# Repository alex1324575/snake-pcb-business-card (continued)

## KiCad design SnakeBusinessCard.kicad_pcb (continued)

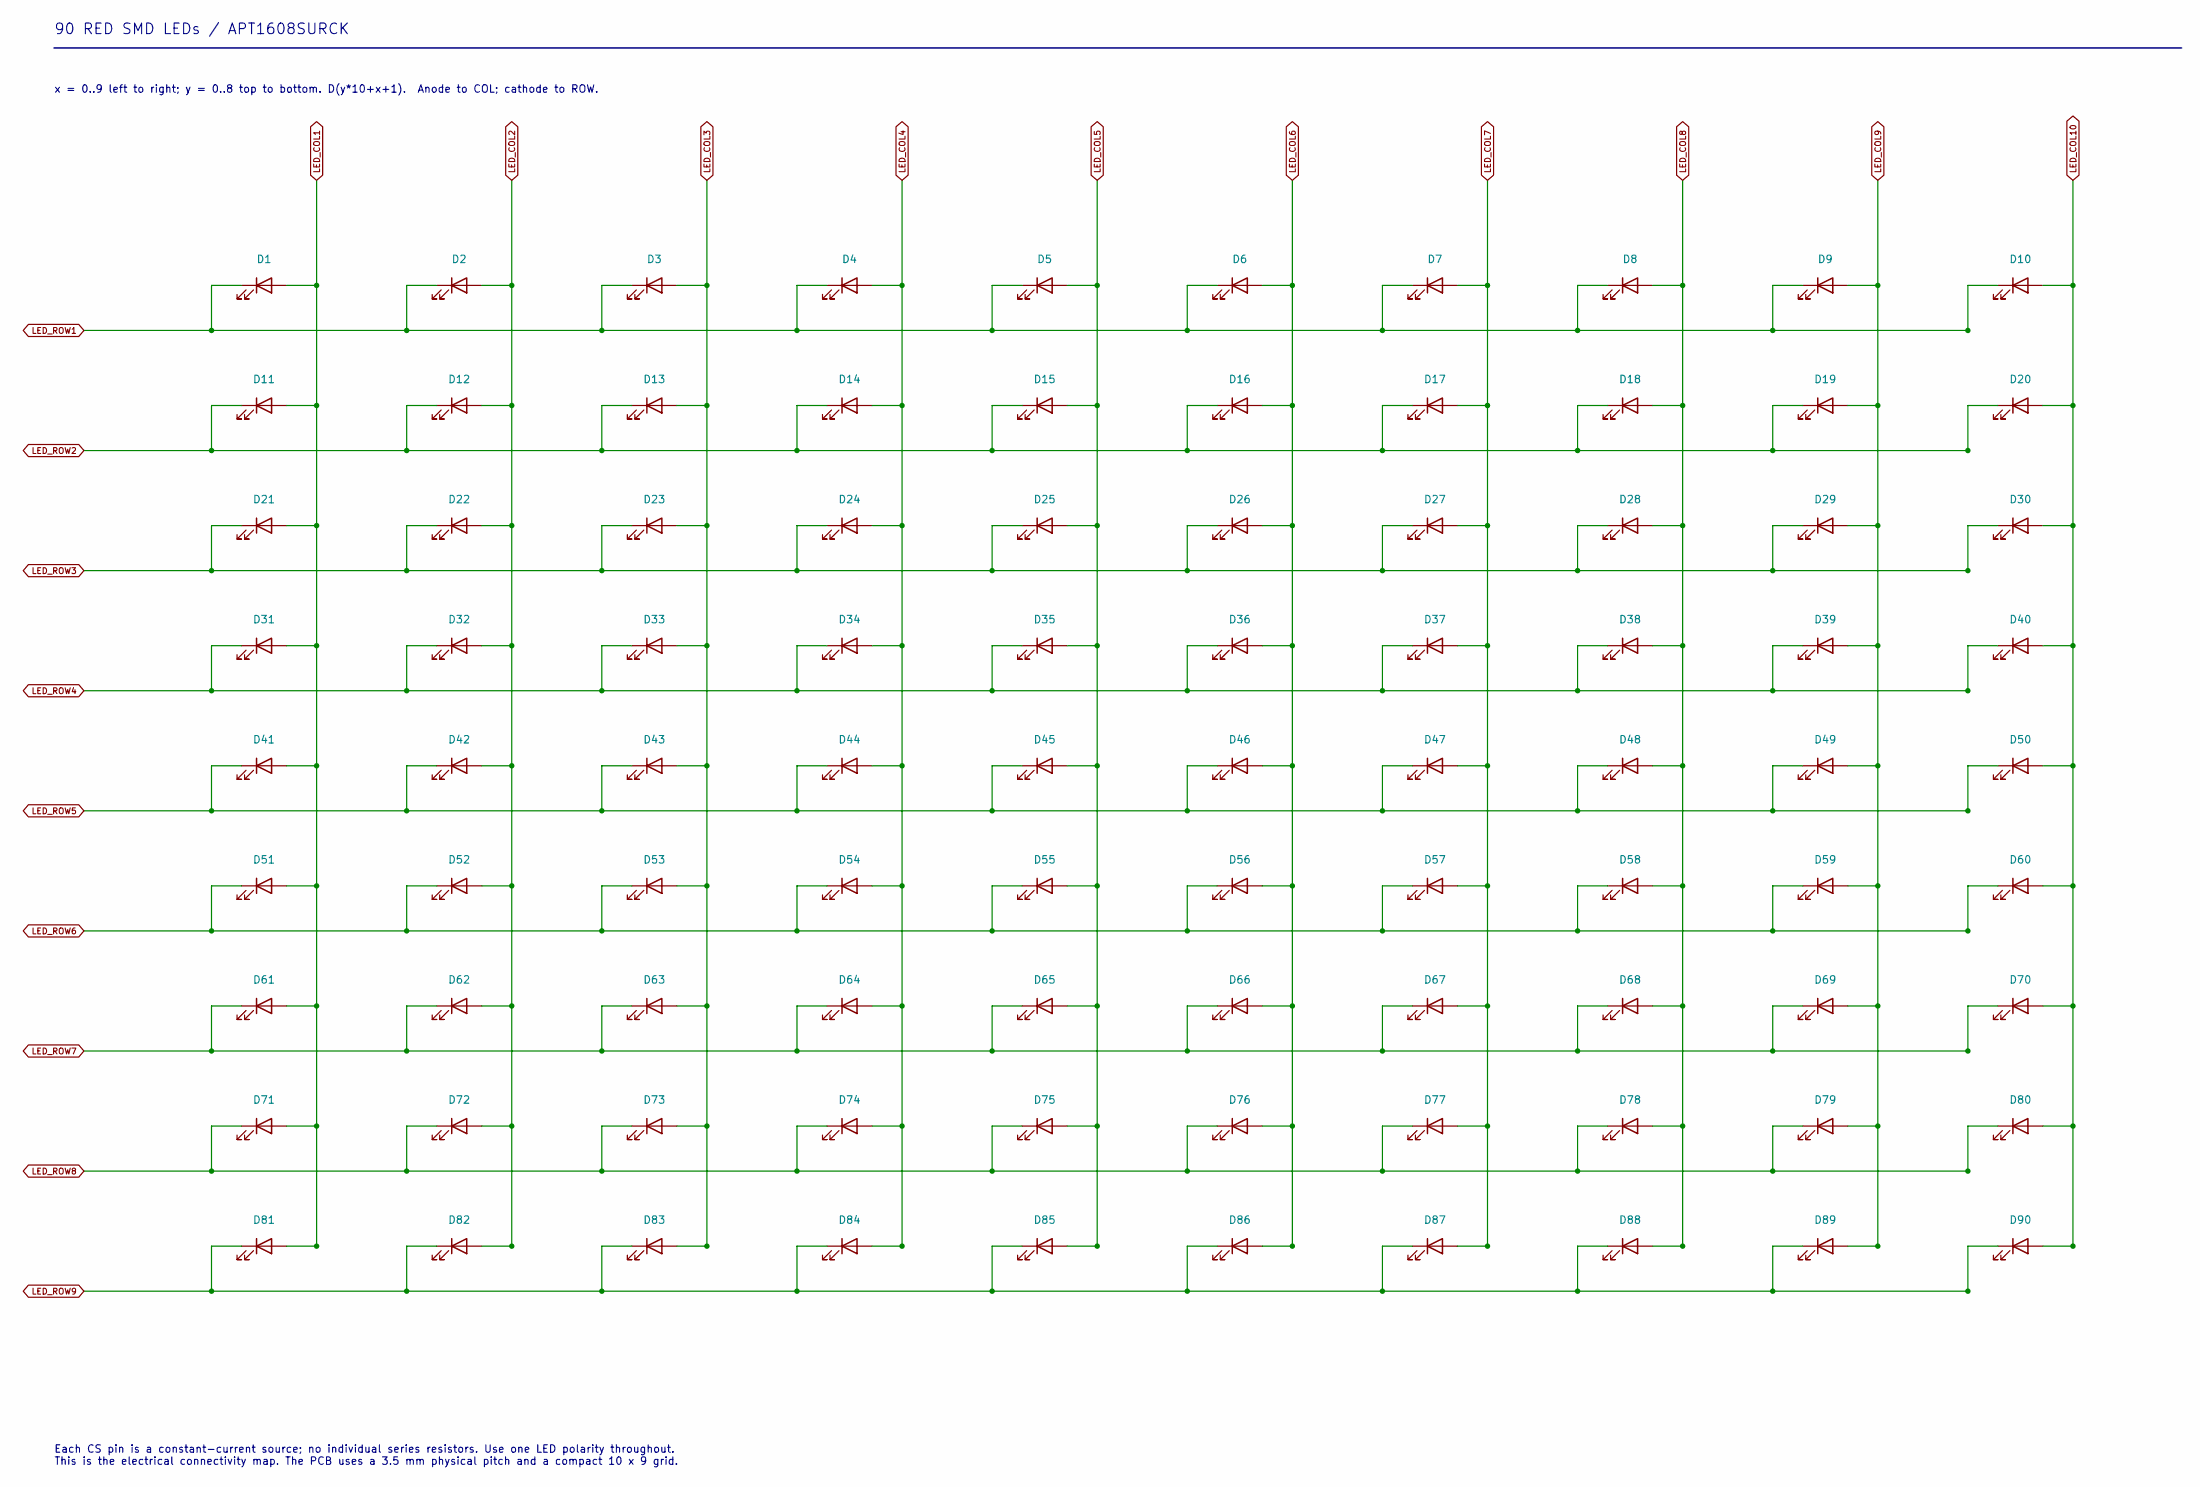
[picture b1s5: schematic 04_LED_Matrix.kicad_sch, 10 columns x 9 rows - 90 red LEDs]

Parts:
D1, D2, D3, D4, D5, D6, D7, D8, D9, D10, D11, D12, D13, D14, D15, D16, D17, D18, D19, D20, D21, D22, D23, D24, D25, D26, D27, D28, D29, D30, D31, D32, D33, D34, D35, D36, D37, D38, D39, D40, D41, D42, D43, D44, D45, D46, D47, D48, D49, D50, D51, D52, D53, D54, D55, D56, D57, D58, D59, D60, D61, D62, D63, D64, D65, D66, D67, D68, D69, D70, D71, D72, D73, D74, D75, D76, D77, D78, D79, D80, D81, D82, D83, D84, D85, D86, D87, D88, D89, D90: RED; Kingbright_APT1608SURCK; MPN APT1608SURCK

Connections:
LED_COL1: D1.2 (A), D11.2 (A), D21.2 (A), D31.2 (A), D41.2 (A), D51.2 (A), D61.2 (A), D71.2 (A), D81.2 (A); also elsewhere on the board
LED_COL2: D2.2 (A), D12.2 (A), D22.2 (A), D32.2 (A), D42.2 (A), D52.2 (A), D62.2 (A), D72.2 (A), D82.2 (A); also elsewhere on the board
LED_COL3: D3.2 (A), D13.2 (A), D23.2 (A), D33.2 (A), D43.2 (A), D53.2 (A), D63.2 (A), D73.2 (A), D83.2 (A); also elsewhere on the board
LED_COL4: D4.2 (A), D14.2 (A), D24.2 (A), D34.2 (A), D44.2 (A), D54.2 (A), D64.2 (A), D74.2 (A), D84.2 (A); also elsewhere on the board
LED_COL5: D5.2 (A), D15.2 (A), D25.2 (A), D35.2 (A), D45.2 (A), D55.2 (A), D65.2 (A), D75.2 (A), D85.2 (A); also elsewhere on the board
LED_COL6: D6.2 (A), D16.2 (A), D26.2 (A), D36.2 (A), D46.2 (A), D56.2 (A), D66.2 (A), D76.2 (A), D86.2 (A); also elsewhere on the board
LED_COL7: D7.2 (A), D17.2 (A), D27.2 (A), D37.2 (A), D47.2 (A), D57.2 (A), D67.2 (A), D77.2 (A), D87.2 (A); also elsewhere on the board
LED_COL8: D8.2 (A), D18.2 (A), D28.2 (A), D38.2 (A), D48.2 (A), D58.2 (A), D68.2 (A), D78.2 (A), D88.2 (A); also elsewhere on the board
LED_COL9: D9.2 (A), D19.2 (A), D29.2 (A), D39.2 (A), D49.2 (A), D59.2 (A), D69.2 (A), D79.2 (A), D89.2 (A); also elsewhere on the board
LED_COL10: D10.2 (A), D20.2 (A), D30.2 (A), D40.2 (A), D50.2 (A), D60.2 (A), D70.2 (A), D80.2 (A), D90.2 (A); also elsewhere on the board
LED_ROW1: D1.1 (K), D2.1 (K), D3.1 (K), D4.1 (K), D5.1 (K), D6.1 (K), D7.1 (K), D8.1 (K), D9.1 (K), D10.1 (K); also elsewhere on the board
LED_ROW2: D11.1 (K), D12.1 (K), D13.1 (K), D14.1 (K), D15.1 (K), D16.1 (K), D17.1 (K), D18.1 (K), D19.1 (K), D20.1 (K); also elsewhere on the board
LED_ROW3: D21.1 (K), D22.1 (K), D23.1 (K), D24.1 (K), D25.1 (K), D26.1 (K), D27.1 (K), D28.1 (K), D29.1 (K), D30.1 (K); also elsewhere on the board
LED_ROW4: D31.1 (K), D32.1 (K), D33.1 (K), D34.1 (K), D35.1 (K), D36.1 (K), D37.1 (K), D38.1 (K), D39.1 (K), D40.1 (K); also elsewhere on the board
LED_ROW5: D41.1 (K), D42.1 (K), D43.1 (K), D44.1 (K), D45.1 (K), D46.1 (K), D47.1 (K), D48.1 (K), D49.1 (K), D50.1 (K); also elsewhere on the board
LED_ROW6: D51.1 (K), D52.1 (K), D53.1 (K), D54.1 (K), D55.1 (K), D56.1 (K), D57.1 (K), D58.1 (K), D59.1 (K), D60.1 (K); also elsewhere on the board
LED_ROW7: D61.1 (K), D62.1 (K), D63.1 (K), D64.1 (K), D65.1 (K), D66.1 (K), D67.1 (K), D68.1 (K), D69.1 (K), D70.1 (K); also elsewhere on the board
LED_ROW8: D71.1 (K), D72.1 (K), D73.1 (K), D74.1 (K), D75.1 (K), D76.1 (K), D77.1 (K), D78.1 (K), D79.1 (K), D80.1 (K); also elsewhere on the board
LED_ROW9: D81.1 (K), D82.1 (K), D83.1 (K), D84.1 (K), D85.1 (K), D86.1 (K), D87.1 (K), D88.1 (K), D89.1 (K), D90.1 (K); also elsewhere on the board

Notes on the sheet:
90 RED SMD LEDs / APT1608SURCK
x = 0..9 left to right; y = 0..8 top to bottom. D(y*10+x+1). Anode to COL; cathode to ROW.
Each CS pin is a constant-current source; no individual series resistors. Use one LED polarity throughout. This is the electrical connectivity map. The PCB uses a 3.5 mm physical pitch and a compact 10 x 9 grid.

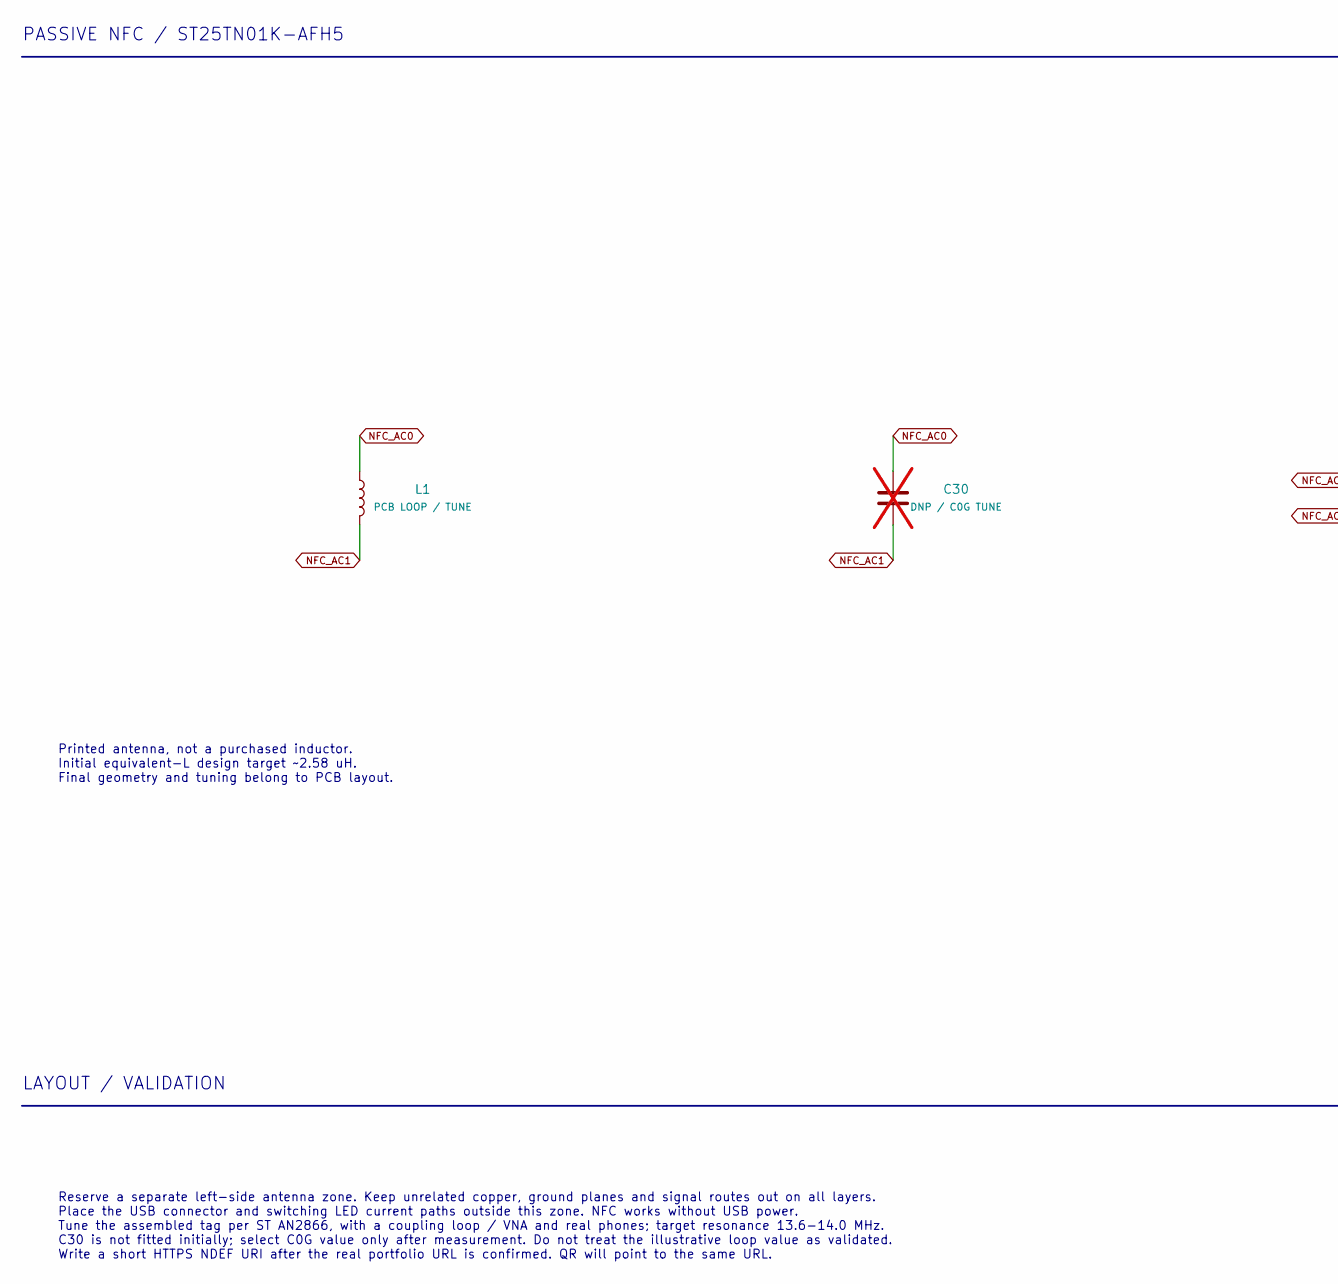
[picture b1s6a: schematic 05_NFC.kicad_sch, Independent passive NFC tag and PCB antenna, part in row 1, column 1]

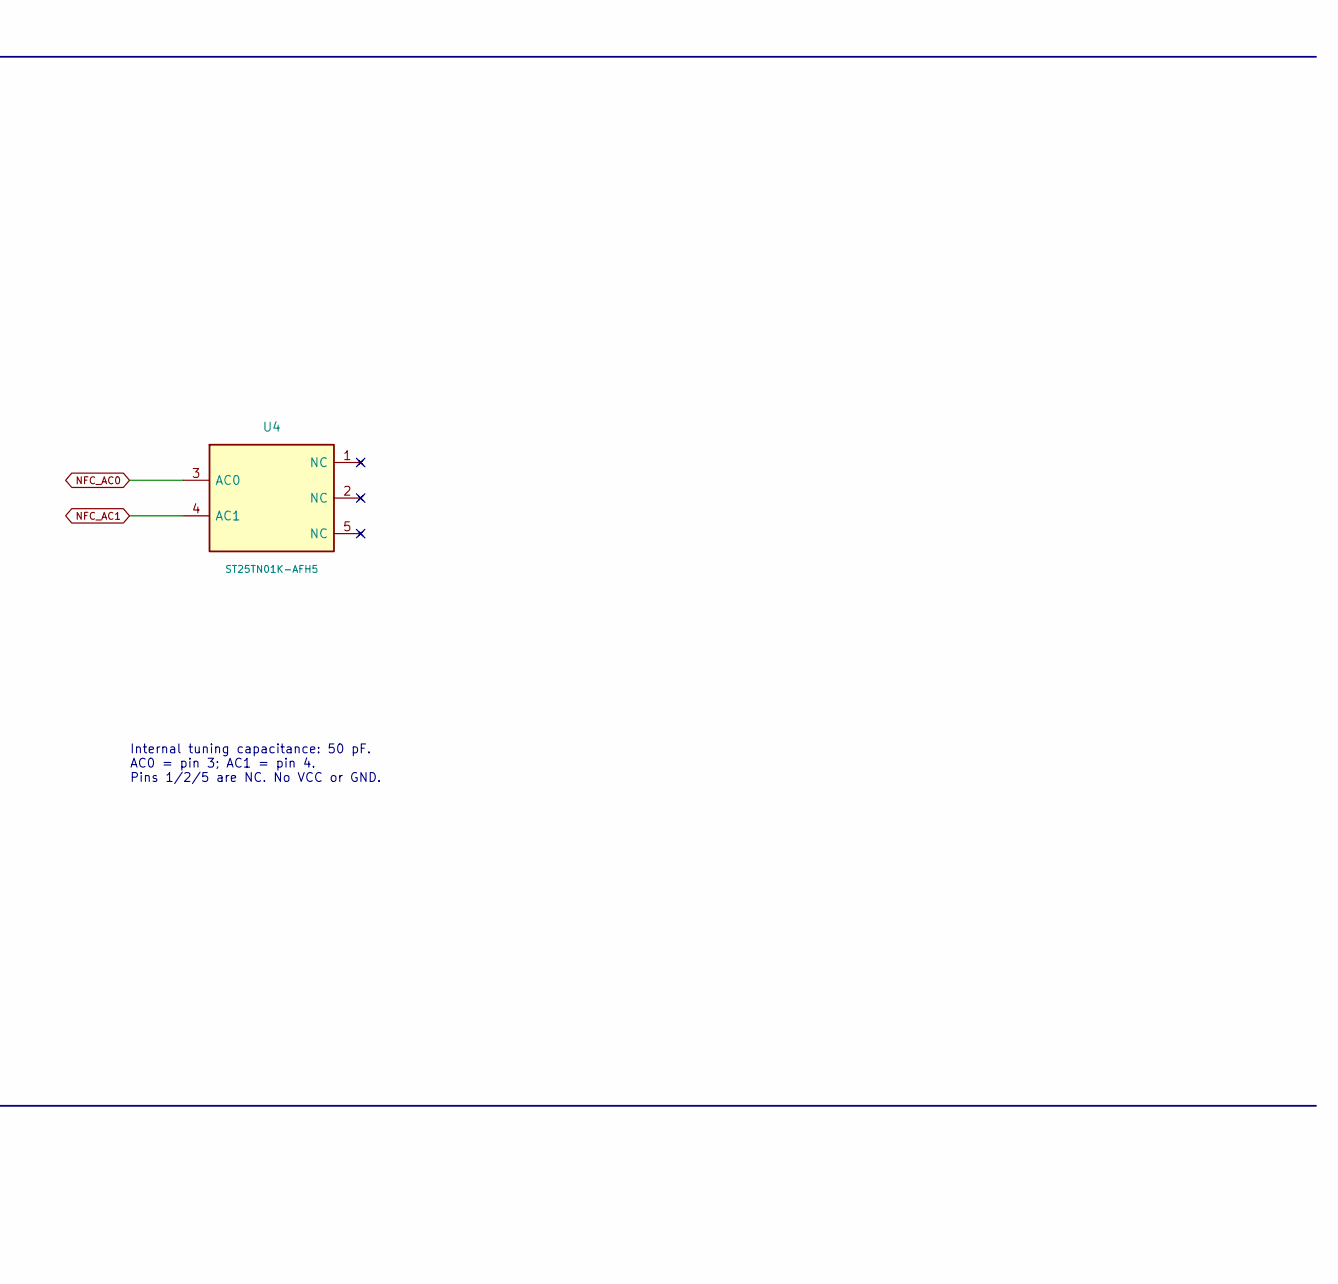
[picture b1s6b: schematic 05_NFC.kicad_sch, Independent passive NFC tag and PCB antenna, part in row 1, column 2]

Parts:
C30: DNP / C0G TUNE; C_0603_1608Metric; not fitted
L1: PCB LOOP / TUNE
U4: ST25TN01K-AFH5; ST25TN01K_UFDFPN5_1.7x1.4mm; MPN ST25TN01K-AFH5

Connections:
NFC_AC0: C30.1, L1.1, U4.3 (AC0); also elsewhere on the board
NFC_AC1: C30.2, L1.2, U4.4 (AC1); also elsewhere on the board

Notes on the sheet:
PASSIVE NFC / ST25TN01K-AFH5
Printed antenna, not a purchased inductor. Initial equivalent-L design target ~2.58 uH. Final geometry and tuning belong to PCB layout.
Internal tuning capacitance: 50 pF. AC0 = pin 3; AC1 = pin 4. Pins 1/2/5 are NC. No VCC or GND.
LAYOUT / VALIDATION
Reserve a separate left-side antenna zone. Keep unrelated copper, ground planes and signal routes out on all layers. Place the USB connector and switching LED current paths outside this zone. NFC works without USB power. Tune the assembled tag per ST AN2866, with a coupling loop / VNA and real phon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

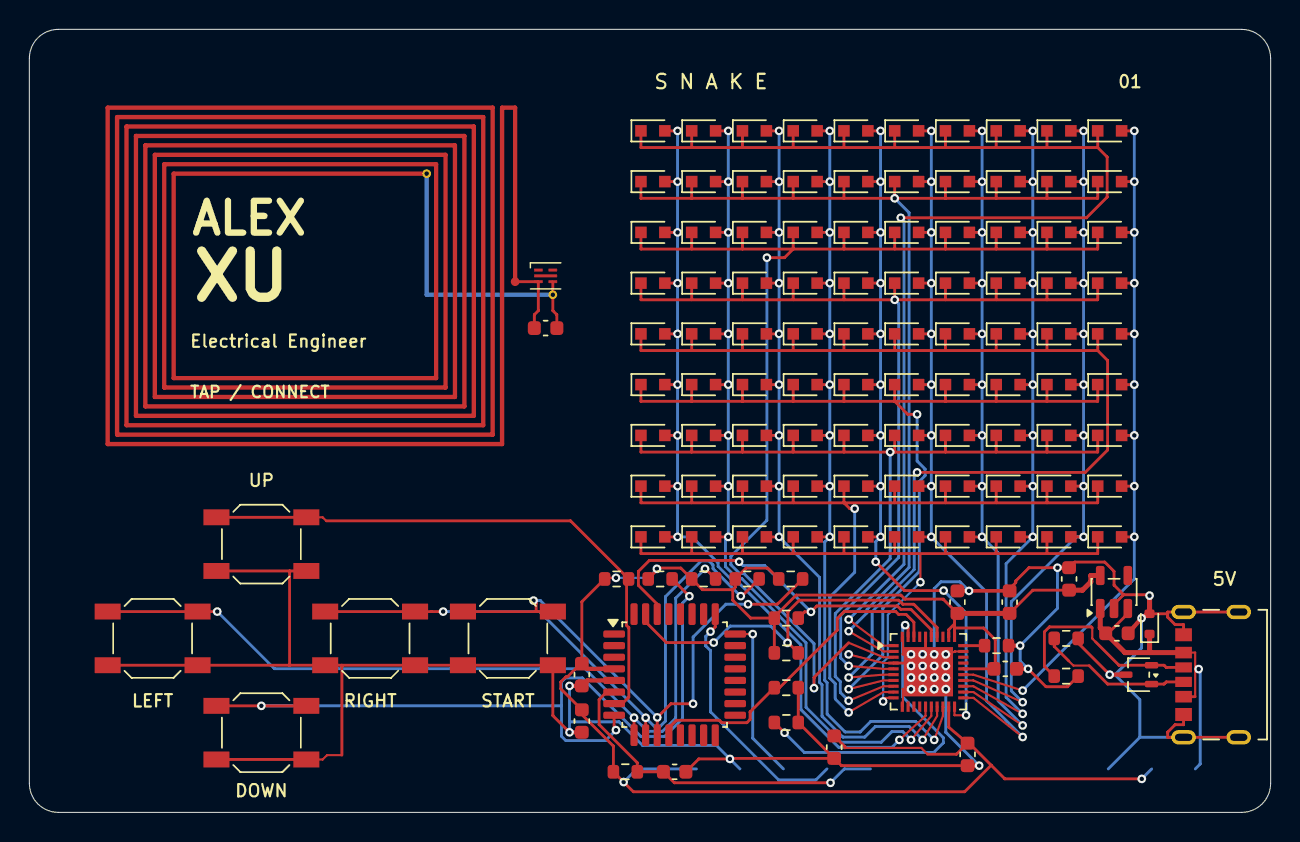
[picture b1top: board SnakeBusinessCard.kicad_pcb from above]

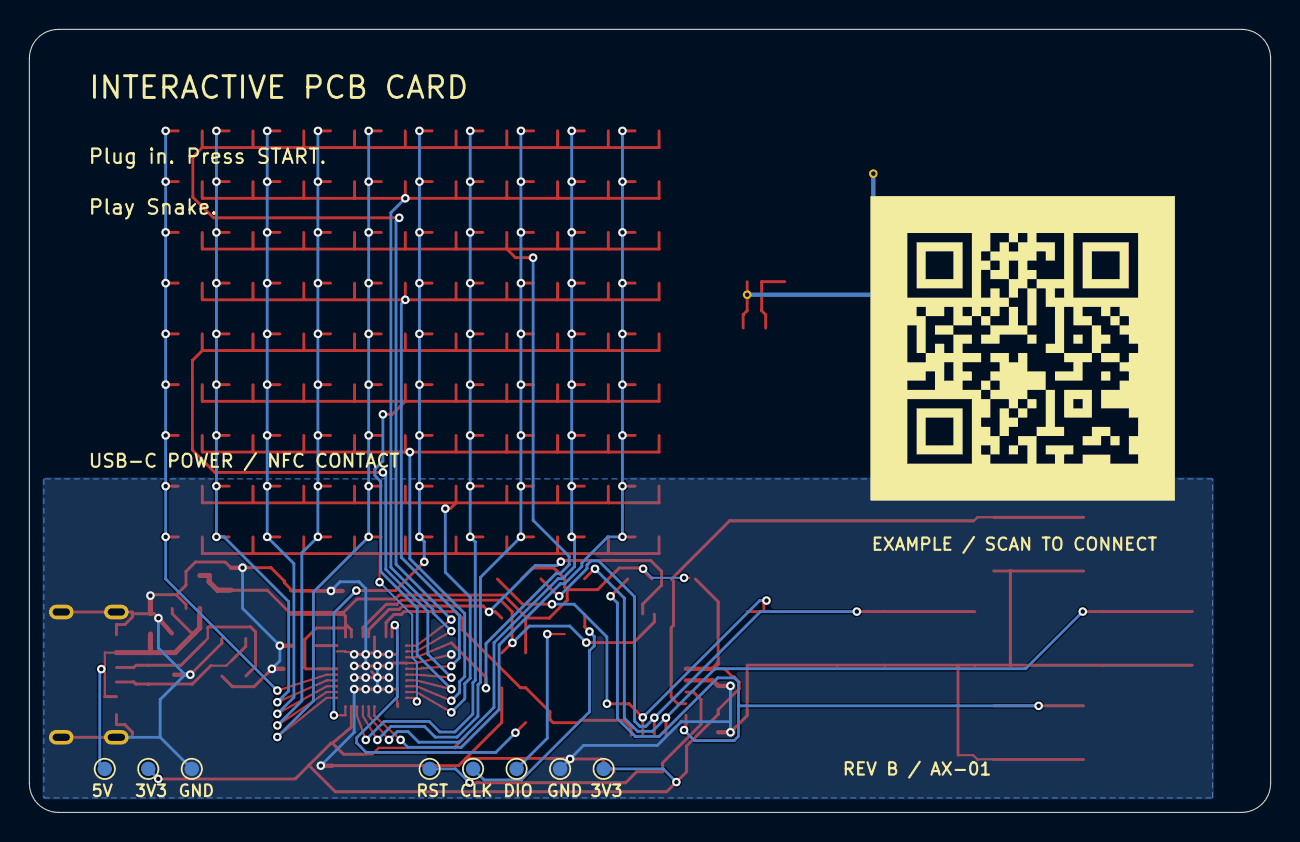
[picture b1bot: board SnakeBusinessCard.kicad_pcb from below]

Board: 2 copper layers, 85.6 x 54.0 mm, 136 parts (9 on the bottom side), 39 nets.

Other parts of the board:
NT1: NFC_PRINTED_COIL_8T_UNTUNED
QR1: Example QR / https://example.com/; Example_QR_21mm_BSilk

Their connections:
NFC_AC0: NT1.1; also elsewhere on the board
NFC_AC1: NT1.2; also elsewhere on the board

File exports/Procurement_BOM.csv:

References,Quantity per board,Manufacturer,MPN,Description,Footprint,Datasheet,Review status,Open items
U1,1,STMicroelectronics,STM32G030K8T6,"Cortex-M0+ MCU, 64 KB Flash, 8 KB SRAM, LQFP32",Package_QFP:LQFP-32_7x7mm_P0.8mm,https://www.st.com/resource/en/datasheet/stm32g030k8.pdf,Document reviewed; assembly and bench open,"Assembler acceptance of KiCad lands; power-up, SWD, reset, GPIO and watchdog tests."
U2,1,Lumissil Microsystems,IS31FL3737-QFLS4-TR,"144-channel matrix LED driver, QFN40 with exposed pad",SnakeCard:IS31FL3737_QFN40_5x5mm_P0.4mm_EP3.4mm,https://www.lumissil.com/assets/pdf/core/IS31FL3737_DS.pdf,Document reviewed; assembly and bench open,QFN via/paste process; LED current and thermal measurements; I2C rise/fall <=300 ns at U2.
U3,1,Texas Instruments,TLV75533PDBVR,"3.3 V fixed LDO, DBV SOT-23-5",Package_TO_SOT_SMD:SOT-23-5,https://www.ti.com/lit/ds/symlink/tlv755p.pdf,Document reviewed; capacitor and bench open,"Effective C1/C2 capacitance; stability, startup and thermal measurement; input transient qualification."
U4,1,STMicroelectronics,ST25TN01K-AFH5,"Passive NFC Type 2 tag, 50 pF option, UFDFPN5",SnakeCard:ST25TN01K_UFDFPN5_1.7x1.4mm,https://www.st.com/resource/en/datasheet/st25tn01k.pdf,Document reviewed; RF function open,Antenna measurement/tuning; physical tag write/read and phone range tests.
U5,1,Texas Instruments,TPD2E2U06DCKR,"Two-channel CC-line ESD protection, DCK SC70-3",Package_TO_SOT_SMD:SOT-323_SC-70,https://www.ti.com/lit/ds/symlink/tpd2e2u06.pdf,Document reviewed; transient qualification open,Board-level ESD and hot-plug tests; no DC overvoltage protection claim.
D91,1,Texas Instruments,TPD1E10B06DYAR,"Bidirectional VBUS ESD protection, DYA SOD-523",Diode_SMD:D_SOD-523,https://www.ti.com/lit/ds/symlink/tpd1e10b06.pdf,Document reviewed; protection coordination open,Published clamp exceeds LDO absolute maximum; measure input transient stress and revise protection if necessary.
J1,1,Same Sky,UJC-HP-3-SMT-TR,"USB-C power-only receptacle for 0.8 mm PCB, six contacts and four shell anchors",SnakeCard:CUI_UJC-HP-3-SMT-TR,https://www.sameskydevices.com/product/resource/ujc-hp-3-smt-tr.pdf,Drawing reviewed; mechanical fit open,"Finished plated slots, shell protrusion and real plug clearance; assembler process acceptance."
"SW1, SW2, SW3, SW4, SW5",5,Alps Alpine,SKQGABE010,"5.2 mm tactile switch, 1.5 mm height, 1.57 N, with stem",Button_Switch_SMD:SW_SPST_SKQG_WithStem,https://tech.alpsalpine.com/cms.media/SKQGAB_KQG_719_EN_cc4e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,Document reviewed; assembly issue open,Resolve switch-area through-via/flux-ingress restriction before assembly; verify contact and debounce on sample.
"D1, D2, D3, D4, D5, D6, D7, D8, D9, D10, D11, D12, D13, D14, D15, D16, D17, D18, D19, D20, D21, D22, D23, D24, D25, D26, D27, D28, D29, D30, D31, D32, D33, D34, D35, D36, D37, D38, D39, D40, D41, D42, D43, D44, D45, D46, D47, D48, D49, D50, D51, D52, D53, D54, D55, D56, D57, D58, D59, D60, D61, D62, D63, D64, D65, D66, D67, D68, D69, D70, D71, D72, D73, D74, D75, D76, D77, D78, D79, D80, D81, D82, D83, D84, D85, D86, D87, D88, D89, D90",90,Kingbright,APT1608SURCK,"Red LED, 0603, 1.6 x 0.8 x 0.75 mm",SnakeCard:Kingbright_APT1608SURCK,https://www.kingbrightusa.com/images/catalog/SPEC/APT1608SURCK.pdf,Document reviewed; optical and thermal open,"Polarity and reel orientation; MSL/reflow handling; low-rail/cold VF headroom, brightness and ghosting."
"C1, C2, C23, C24",4,TDK,C1608X7R1V105K080AC,"1 uF X7R ceramic capacitor, 0603 / 1608 metric, 35 V, +/-10%, paper tape on 180 mm reel",Capacitor_SMD:C_0603_1608Metric,https://product.tdk.com/system/files/dam/doc/product/capacit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,CONDITIONAL_EFFECTIVE_CAPACITANCE,"Nominal capacitance and geometry unchanged; rating raised from 10 V. C1 is on VBUS; C2/C23/C24 are on 3.3 V. Exact-part DC-bias characterization is linked but numerical values at 5 V/5.5 V and 3.3 V were not obtained. C1/C2 require more than 0.47 uF effective at regulator pins after bias, tolerance, temperature and aging. Existing IPC lands differ from manufacturer reflow recommendations; assembler process approval remains open."
"C10, C12, C20, C21, C22",5,TDK,C1608X7R1H104K080AA,"100 nF X7R ceramic capacitor, 0603 / 1608 metric, 50 V, +/-10%, paper tape on 180 mm reel",Capacitor_SMD:C_0603_1608Metric,https://product.tdk.com/info/en/documents/chara_sheet/C1608X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,CONDITIONAL_BOARD_VALIDATION,Nominal capacitance and geometry unchanged; rating raised from 10 V. Voltage stress is 6.6% of rating at 3.3 V. Biased capacitance not numerically qualified. Verify decoupling and NRST response on first board. Existing IPC lands differ from manufacturer reflow recommendations; assembler process approval remains open.
C11,1,Murata Manufacturing,GRM188Z71C475KE21D,"4.7 uF X7R(Murata) ceramic capacitor, 0603 / 1608 metric, 16 V, +/-10%, D suffix 180 mm paper-tape reel",Capacitor_SMD:C_0603_1608Metric,https://search.murata.co.jp/Ceramy/image/img/A01X/G101/ENG/G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,CONDITIONAL_EFFECTIVE_CAPACITANCE,"Nominal capacitance and geometry unchanged; rating raised from 10 V. X7R(Murata) uses a temperature characteristic evaluated with half-rated DC bias, not the ordinary EIA X7R condition. Record exact-part effective capacitance at 3.3 V before final qualification. The compact schematic value omits the dielectric, which remains mandatory in this purchasing description."
"R1, R2",2,Panasonic Industry,ERJ3EKF5101V,"5.1 kohm precision thick-film resistor, 0603, +/-1%, 0.1 W at 70 C, +/-100 ppm/K, V suffix paper tape",Resistor_SMD:R_0603_1608Metric,https://industrial.panasonic.com/cdbs/www-data/pdf/RDA0000/A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,DOCUMENT_REVIEW_COMPLETE,"USB CC pull-downs. At a conservative 5.5 V across each resistor and -1% R, power is 5.99 mW versus 100 mW at 70 C. Initial resistance is 5.049 to 5.151 kohm. Temperature, aging and assembled USB attach behavior remain additional checks."
"R10, R11, R12, R13, R14, R15, R23",7,Panasonic Industry,ERJ3EKF1002V,"10 kohm precision thick-film resistor, 0603, +/-1%, 0.1 W at 70 C, +/-100 ppm/K, V suffix paper tape",Resistor_SMD:R_0603_1608Metric,https://industrial.panasonic.com/cdbs/www-data/pdf/RDA0000/A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,DOCUMENT_REVIEW_COMPLETE,"Nominal resistance unchanged; tolerance explicitly fixed to 1%. At 3.6 V and -1% R, power is 1.31 mW. Functional reset, button and driver configuration checks remain first-board tasks."
"R20, R21",2,Panasonic Industry,ERJ3EKF2201V,"2.2 kohm precision thick-film resistor, 0603, +/-1%, 0.1 W at 70 C, +/-100 ppm/K, V suffix paper tape",Resistor_SMD:R_0603_1608Metric,https://industrial.panasonic.com/cdbs/www-data/pdf/RDA0000/A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,DOCUMENT_REVIEW_COMPLETE,"I2C pull-ups. At 3.6 V and -1% R, power is 5.95 mW. Lowest DC working-voltage screening bound sqrt(0.1 W * 2178 ohm) is 14.8 V. Board bus capacitance, sink level and rise/fall timing must be measured."
R22,1,Panasonic Industry,ERJ3EKF1003V,"100 kohm precision thick-film resistor, 0603, +/-1%, 0.1 W at 70 C, +/-100 ppm/K, V suffix paper tape",Resistor_SMD:R_0603_1608Metric,https://industrial.panasonic.com/cdbs/www-data/pdf/RDA0000/A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,DOCUMENT_REVIEW_COMPLETE,"LED_EN pull-down. At 3.6 V and -1% R, power is 0.131 mW. Verify the display remains off through reset and power ramps on first board."
R24,1,Panasonic Industry,ERJ3EKF2002V,"20 kohm precision thick-film resistor, 0603, +/-1%, 0.1 W at 70 C, +/-100 ppm/K, V suffix paper tape",Resistor_SMD:R_0603_1608Metric,https://industrial.panasonic.com/cdbs/www-data/pdf/RDA0000/A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,DOCUMENT_REVIEW_COMPLETE,"LED-driver current-setting resistor. At a conservative 3.6 V across it and -1% R, power is 0.655 mW. Initial R range 19.8 to 20.2 kohm adds about -0.99%/+1.01% to inverse-R current variation before driver, temperature and aging tolerances. Verify channel current and supply load on first board."

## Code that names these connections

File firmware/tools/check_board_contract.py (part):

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        controls.append((net, str(7 + index), f'PA{index}', f'SW{index + 1}'))
    macro('BUTTON_MASK', 31)
    for number, gpio, net, driver_number, driver_function, resistor in (
            (30, 'PB6', 'I2C_SCL', 35, 'SCL', 'R20'),
            (31, 'PB7', 'I2C_SDA', 34, 'SDA', 'R21')):
        pin('U1', number, net, gpio)
        pin('U2', driver_number, net, driver_function)
        pin(resistor, 1, '+3V3')
        pin(resistor, 2, net)
        value(resistor, '2.2k 1%')
        controls.append((net, str(number), gpio, 'U2.' + str(driver_number)))
    pin('U1', 12, 'LED_EN', 'PA5')
    pin('U2', 38, 'LED_EN', '~{SDB}')
    pin('R22', 1, 'LED_EN')
    pin('R22', 2, 'GND')
    value('R22', '100k 1%')
    controls.append(('LED_EN', '12', 'PA5', 'U2.38'))
    for number, function, net, tp in ((24, 'PA13', 'SWDIO', 'TP6'),
                                       (25, 'PA14', 'SWCLK', 'TP7'),
                                       (6, 'NRST', 'NRST', 'TP8')):
        pin('U1', number, net, function)
        pin(tp, 1, net)
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
    init = body('board_init')
    required = {
        'Buttons read PA0..PA4 active-low':
            (body('board_buttons'), 'return(uint8_t)(~SC_GPIO_IDR(SC_GPIOA)&UINT32_C(0x1f));'),
        'SDB callback drives port A':
            (body('board_sdb'), 'SC_GPIO_BSRR(SC_GPIOA)=high?SDB_PIN:SDB_PIN<<16;'),
        'SDB is preloaded low before configuration':
            (init, 'SC_GPIO_BSRR(SC_GPIOA)=SDB_PIN<<16;'),
        'I2C PB6/PB7 are open-drain':
            (init, 'SC_GPIO_OTYPER(SC_GPIOB)|=BUS_PINS;'),
        'I2C PB6/PB7 select AF6':
            (init, 'SC_GPIO_AFRL(SC_GPIOB)=(SC_GPIO_AFRL(SC_GPIOB)&~UINT32_C(0xff000000))|UINT32_C(0x66000000);'),
    }
    for name, (scope, snippet) in required.items():
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def negative_controls(netlist, board, macros):
    scenarios = []
    n, b, m = copy.deepcopy(netlist), copy.deepcopy(board), dict(macros)
    n['pins'][('D7', '2')]['net'] = 'LED_COL6'
    scenarios.append(('LED anode on wrong column', n, b, m))
    n, b, m = copy.deepcopy(netlist), copy.deepcopy(board), dict(macros)
    b['D1']['x'], b['D10']['x'] = b['D10']['x'], b['D1']['x']
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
